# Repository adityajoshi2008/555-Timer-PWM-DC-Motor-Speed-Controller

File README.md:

# 555-Timer-PWM-DC-Motor-Speed-Controller
**555 timer-based PWM DC motor speed controller designed and developed in KiCAD for practical motor speed control.
# DC Motor Speed Controller ⚙️

A PCB design project for controlling the speed of a DC motor using a **555 timer-based PWM circuit**. The schematic and PCB were designed in **KiCad**, with the goal of creating a compact and practical motor speed controller.

## 🔧 Project Overview

The controller uses an **NE555P timer** to generate a PWM signal. A potentiometer is used to adjust the PWM duty cycle, which controls the power delivered to the motor and therefore allows its speed to be varied.

The output stage uses a **TIP122 Darlington transistor** to drive the motor, while a **1N4007 diode** provides protection against the motor's inductive voltage spikes.

## 🧩 Main Components

| Component        | Value / Part          |
| ---------------- | --------------------- |
| Timer IC         | NE555P                |
| Power Transistor | TIP122                |
| Potentiometer    | 100kΩ                 |
| Diodes           | 1N4007                |
| Capacitors       | 100nF, 1000µF         |
| Resistors        | 1kΩ, 2.2kΩ            |
| Indicators       | LED                   |
| Connectors       | 2-pin screw terminals |

## 🛠️ Tools Used

* **KiCad 10**
* Schematic Editor
* PCB Editor
* PCB Layout & Routing
* Gerber Generation

## 📂 Repository Contents

```text
DC-Motor-Speed-Controller/
│
├── DC Motor Speed Controller.kicad_sch
├── DC Motor Speed Controller.kicad_pcb
│
├── Gerbers/
│   └── PCB manufacturing files
│
├── Images/
│   ├── PCB_Front.png
│   └── PCB_Back.png
│
└── README.md
```

## 📚 What I Learned

This project helped me gain practical experience with:

* 555 timer circuits
* PWM-based motor speed control
* Transistor-based motor driving
* Flyback protection for inductive loads
* Schematic design in KiCad
* PCB component placement
* PCB routing
* Generating Gerber files
* Preparing a PCB design for manufacturing

## 🚀 Future Improvements

Possible improvements for a future version include:

* Adding better motor current protection
* Adding a fuse or dedicated protection stage
* Improving thermal management of the power transistor
* Adding reverse-polarity protection
* Testing and documenting the actual motor voltage, current and speed range

## ⚠️ Safety

This controller is intended for suitable **low-voltage DC motor applications**. Use an appropriate DC power supply and ensure that the motor current does not exceed the capabilities of the switching and PCB components.

Do not connect this circuit directly to AC mains.

---

## 👨‍💻 Author

**Aditya Joshi**

B.Tech ECE (Semiconductor)

Interested in **PCB Design, Electronics, VLSI and Embedded Systems**.

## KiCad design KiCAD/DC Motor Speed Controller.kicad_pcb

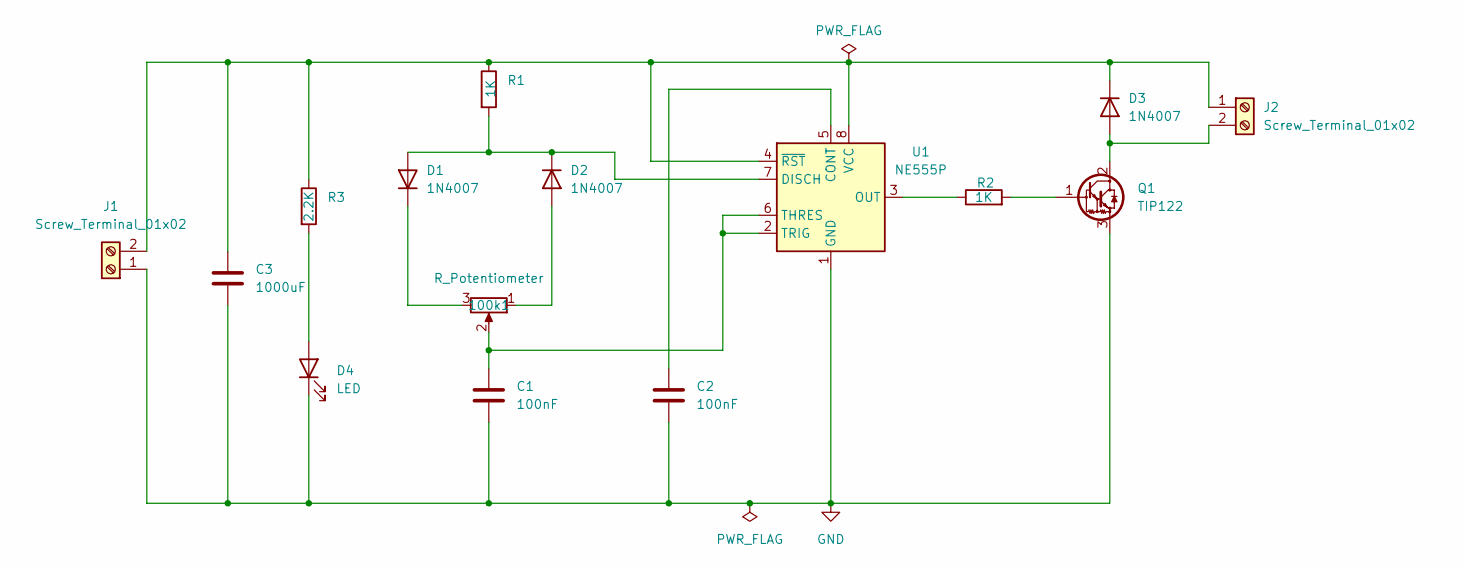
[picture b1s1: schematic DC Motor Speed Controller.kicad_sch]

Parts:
100k1: R_Potentiometer; Potentiometer_Alps_RK163_Single_Horizontal
C1, C2: 100nF; C_Disc_D4.7mm_W2.5mm_P5.00mm
C3: 1000uF; CP_Radial_D10.0mm_P5.00mm
D1, D2, D3: 1N4007; D_DO-41_SOD81_P10.16mm_Horizontal
D4: LED; LED_D5.0mm
J1, J2: Screw_Terminal_01x02; TerminalBlock_MaiXu_MX126-5.0-02P_1x02_P5.00mm
Q1: TIP122; TO-220-3_Vertical
R1, R2: 1K; R_Axial_DIN0204_L3.6mm_D1.6mm_P7.62mm_Horizontal
R3: 2.2K; R_Axial_DIN0204_L3.6mm_D1.6mm_P7.62mm_Horizontal
U1: NE555P; DIP-8_W7.62mm

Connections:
GND: C1.2, C2.2, C3.2, D4.1 (K), J1.1, Q1.3 (E), U1.1 (GND)
unnamed: D1.2 (A), D2.1 (K), R1.2, U1.7 (DISCH)
unnamed: 100k1.3, D1.1 (K)
unnamed: 100k1.1, D2.2 (A)
unnamed: D3.2 (A), J2.2, Q1.2 (C)
unnamed: C3.1, D3.1 (K), J1.2, J2.1, R1.1, R3.1, U1.4 (~RST), U1.8 (VCC)
unnamed: D4.2 (A), R3.2
unnamed: Q1.1 (B), R2.2
unnamed: C2.1, U1.5 (CONT)
unnamed: R2.1, U1.3 (OUT)
unnamed: 100k1.2, C1.1, U1.2 (TRIG), U1.6 (THRES)

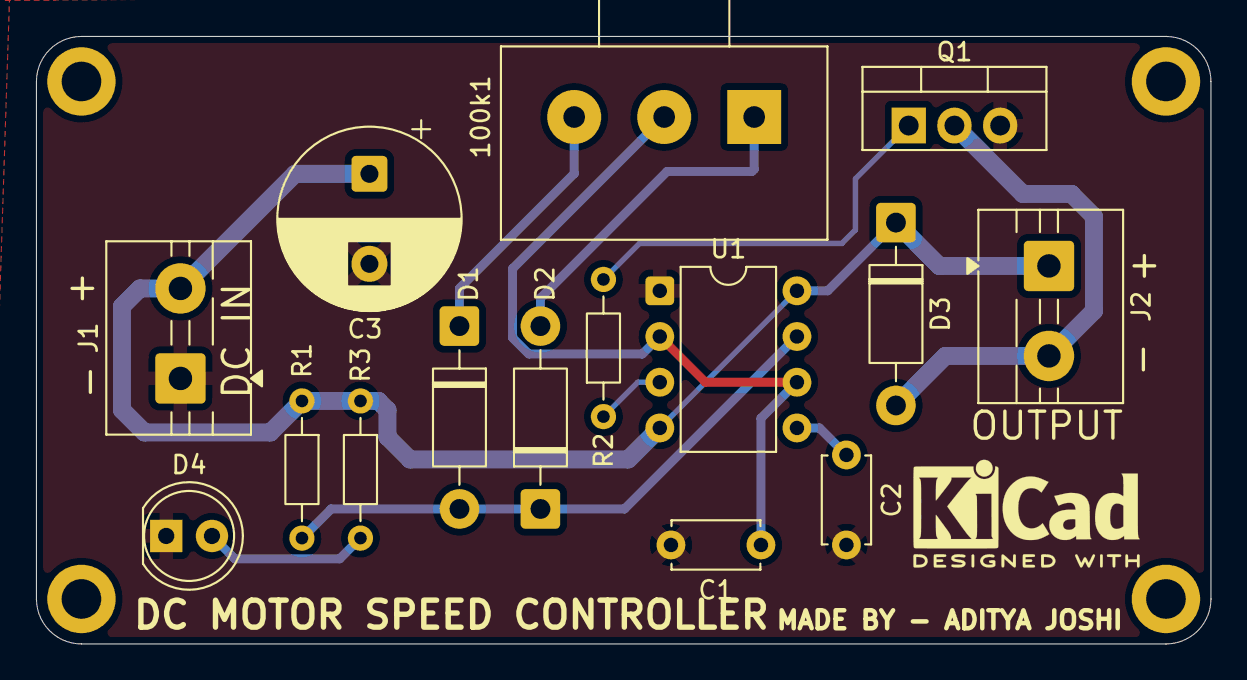
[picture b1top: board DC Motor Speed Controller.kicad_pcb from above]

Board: 2 copper layers, 65.2 x 33.8 mm, 15 parts (0 on the bottom side), 11 nets.
